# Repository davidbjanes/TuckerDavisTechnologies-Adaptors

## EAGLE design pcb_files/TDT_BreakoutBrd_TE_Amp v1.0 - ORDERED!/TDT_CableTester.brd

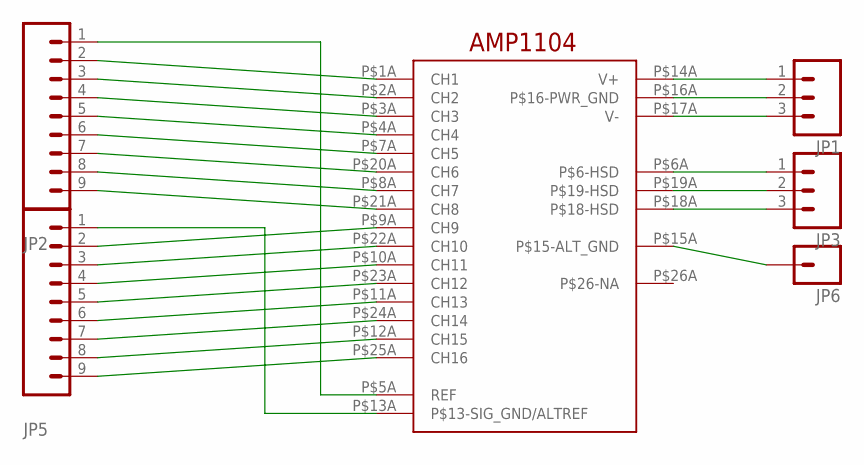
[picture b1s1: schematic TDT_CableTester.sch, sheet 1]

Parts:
JP1, JP3: M03PTH; 1X03
JP2, JP5: M09; 1X09
JP6: M01PTH; 1X01
U$3: AMP1104

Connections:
unnamed: JP2.2, U$3.P$1A (CH1)
unnamed: JP2.3, U$3.P$2A (CH2)
unnamed: JP2.4, U$3.P$3A (CH3)
unnamed: JP2.5, U$3.P$4A (CH4)
unnamed: JP2.6, U$3.P$7A (CH5)
unnamed: JP2.7, U$3.P$20A (CH6)
unnamed: JP2.8, U$3.P$8A (CH7)
unnamed: JP2.9, U$3.P$21A (CH8)
unnamed: JP5.2, U$3.P$9A (CH9)
unnamed: JP5.3, U$3.P$22A (CH10)
unnamed: JP5.4, U$3.P$10A (CH11)
unnamed: JP5.5, U$3.P$23A (CH12)
unnamed: JP5.6, U$3.P$11A (CH13)
unnamed: JP5.7, U$3.P$24A (CH14)
unnamed: JP5.8, U$3.P$12A (CH15)
unnamed: JP5.9, U$3.P$25A (CH16)
unnamed: JP1.1, U$3.P$14A (V+)
unnamed: JP1.2, U$3.P$16A (P$16-PWR_GND)
unnamed: JP1.3, U$3.P$17A (V-)
unnamed: JP6.1, U$3.P$15A (P$15-ALT_GND)
unnamed: JP2.1, U$3.P$5A (REF)
unnamed: JP5.1, U$3.P$13A (P$13-SIG_GND/ALTREF)
unnamed: JP3.1, U$3.P$6A (P$6-HSD)
unnamed: JP3.2, U$3.P$19A (P$19-HSD)
unnamed: JP3.3, U$3.P$18A (P$18-HSD)

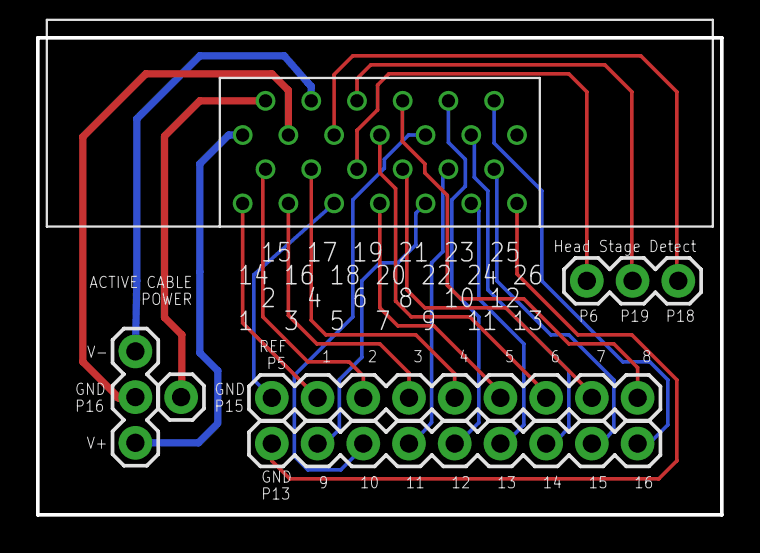
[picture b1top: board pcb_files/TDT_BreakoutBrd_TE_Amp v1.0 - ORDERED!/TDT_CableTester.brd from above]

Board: 2 copper layers, 38.0 x 26.5 mm, 6 parts (0 on the bottom side), 25 nets.

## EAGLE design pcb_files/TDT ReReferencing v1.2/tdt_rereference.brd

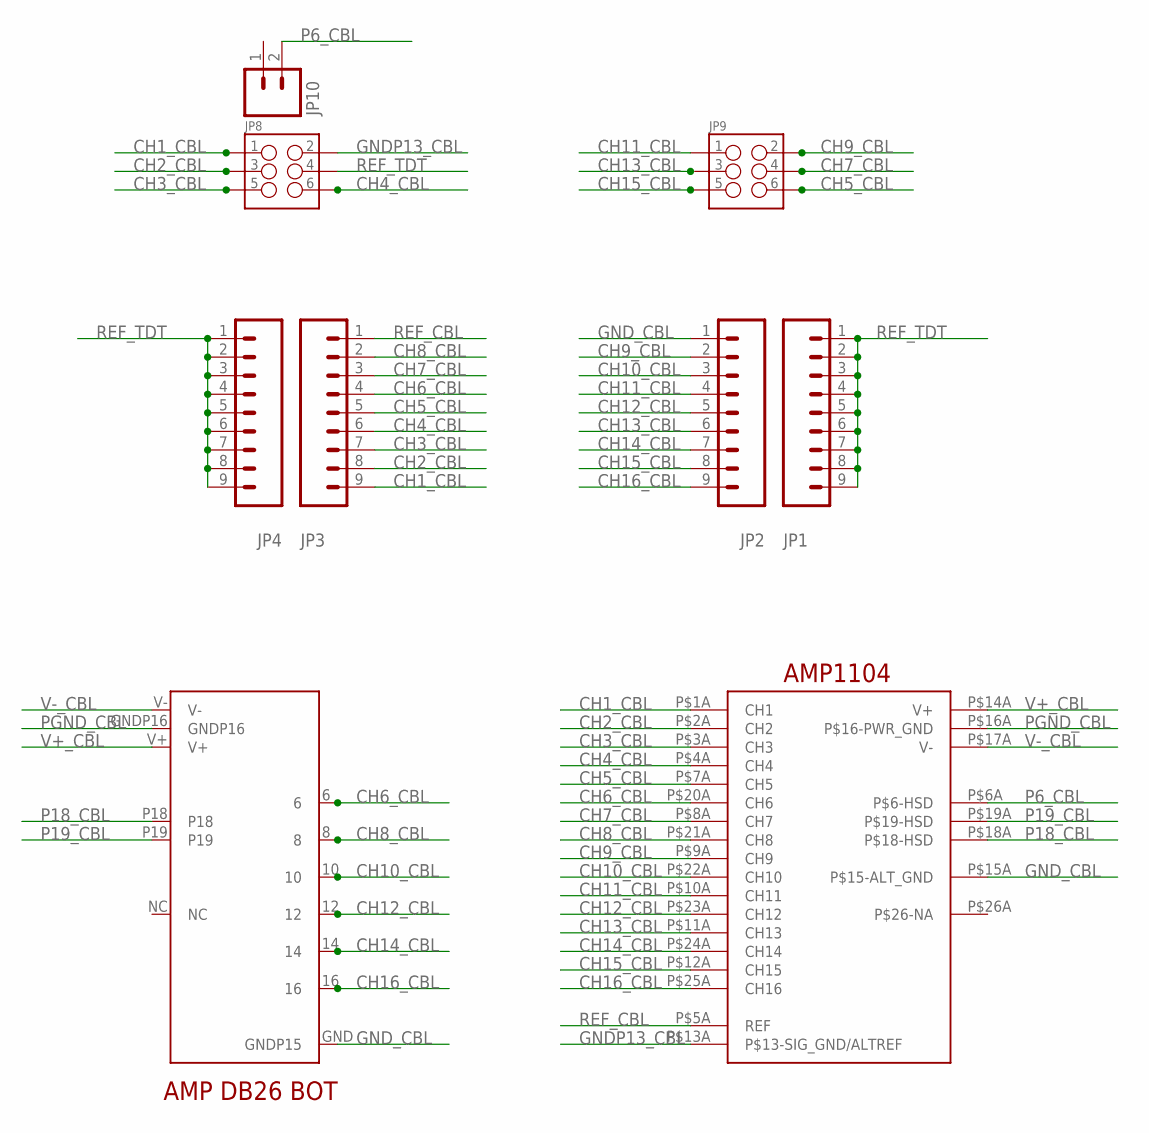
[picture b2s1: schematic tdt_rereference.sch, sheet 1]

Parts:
JP1, JP2, JP3, JP4: M09; 1X09
JP8, JP9: M03X22X3_SILK_MALE_PTH; 2X3
JP10: M02PTH; 1X02
U$1: DB26-MALE-BOT
U$3: AMP1104

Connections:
CH1_CBL: JP3.9, JP8.1, U$3.P$1A (CH1)
CH2_CBL: JP3.8, JP8.3, U$3.P$2A (CH2)
CH3_CBL: JP3.7, JP8.5, U$3.P$3A (CH3)
CH4_CBL: JP3.6, JP8.6, U$3.P$4A (CH4)
CH5_CBL: JP3.5, JP9.6, U$3.P$7A (CH5)
CH6_CBL: JP3.4, U$1.6, U$3.P$20A (CH6)
CH7_CBL: JP3.3, JP9.4, U$3.P$8A (CH7)
CH8_CBL: JP3.2, U$1.8, U$3.P$21A (CH8)
CH9_CBL: JP2.2, JP9.2, U$3.P$9A (CH9)
CH10_CBL: JP2.3, U$1.10, U$3.P$22A (CH10)
CH11_CBL: JP2.4, JP9.1, U$3.P$10A (CH11)
CH12_CBL: JP2.5, U$1.12, U$3.P$23A (CH12)
CH13_CBL: JP2.6, JP9.3, U$3.P$11A (CH13)
CH14_CBL: JP2.7, U$1.14, U$3.P$24A (CH14)
CH15_CBL: JP2.8, JP9.5, U$3.P$12A (CH15)
CH16_CBL: JP2.9, U$1.16, U$3.P$25A (CH16)
GNDP13_CBL: JP8.2, U$3.P$13A (P$13-SIG_GND/ALTREF)
GND_CBL: JP2.1, U$1.GND (GNDP15), U$3.P$15A (P$15-ALT_GND)
P6_CBL: JP10.2, U$3.P$6A (P$6-HSD)
P18_CBL: U$1.P18, U$3.P$18A (P$18-HSD)
P19_CBL: U$1.P19, U$3.P$19A (P$19-HSD)
PGND_CBL: U$1.GNDP16, U$3.P$16A (P$16-PWR_GND)
REF_CBL: JP3.1, U$3.P$5A (REF)
REF_TDT: JP1.1, JP1.2, JP1.3, JP1.4, JP1.5, JP1.6, JP1.7, JP1.8, JP1.9, JP4.1, JP4.2, JP4.3, JP4.4, JP4.5, JP4.6, JP4.7, JP4.8, JP4.9, JP8.4
V+_CBL: U$1.V+, U$3.P$14A (V+)
V-_CBL: U$1.V-, U$3.P$17A (V-)

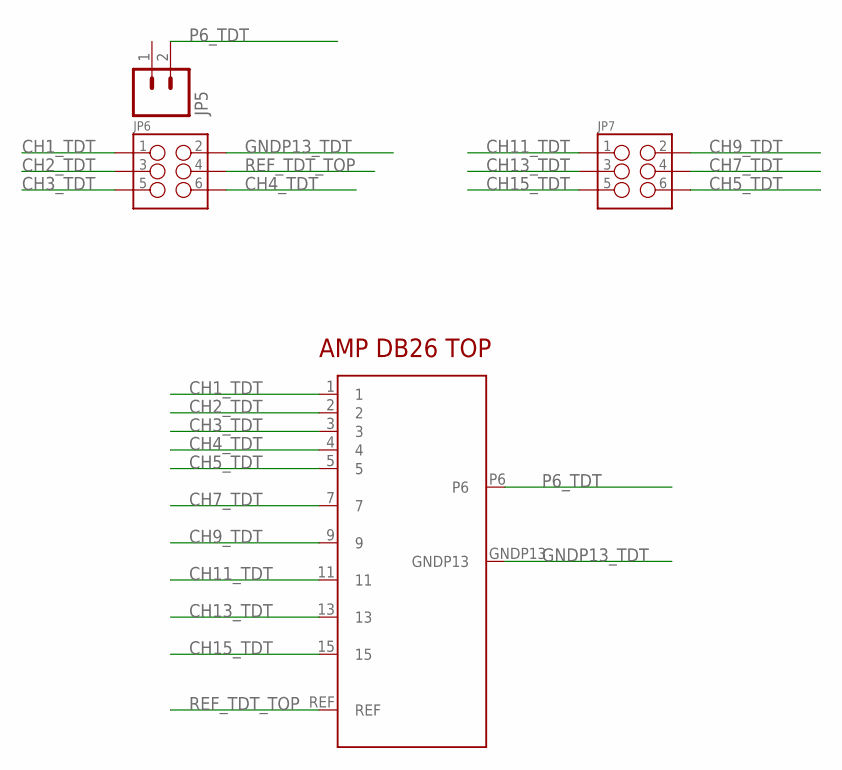
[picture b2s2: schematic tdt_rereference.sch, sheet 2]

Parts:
JP5: M02PTH; 1X02
JP6, JP7: M03X22X3_SILK_MALE_PTH; 2X3
U$2: DB26-MALE-TOP

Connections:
CH1_TDT: JP6.1, U$2.1
CH2_TDT: JP6.3, U$2.2
CH3_TDT: JP6.5, U$2.3
CH4_TDT: JP6.6, U$2.4
CH5_TDT: JP7.6, U$2.5
CH7_TDT: JP7.4, U$2.7
CH9_TDT: JP7.2, U$2.9
CH11_TDT: JP7.1, U$2.11
CH13_TDT: JP7.3, U$2.13
CH15_TDT: JP7.5, U$2.15
GNDP13_TDT: JP6.2, U$2.GNDP13
P6_TDT: JP5.2, U$2.P6
REF_TDT_TOP: JP6.4, U$2.REF

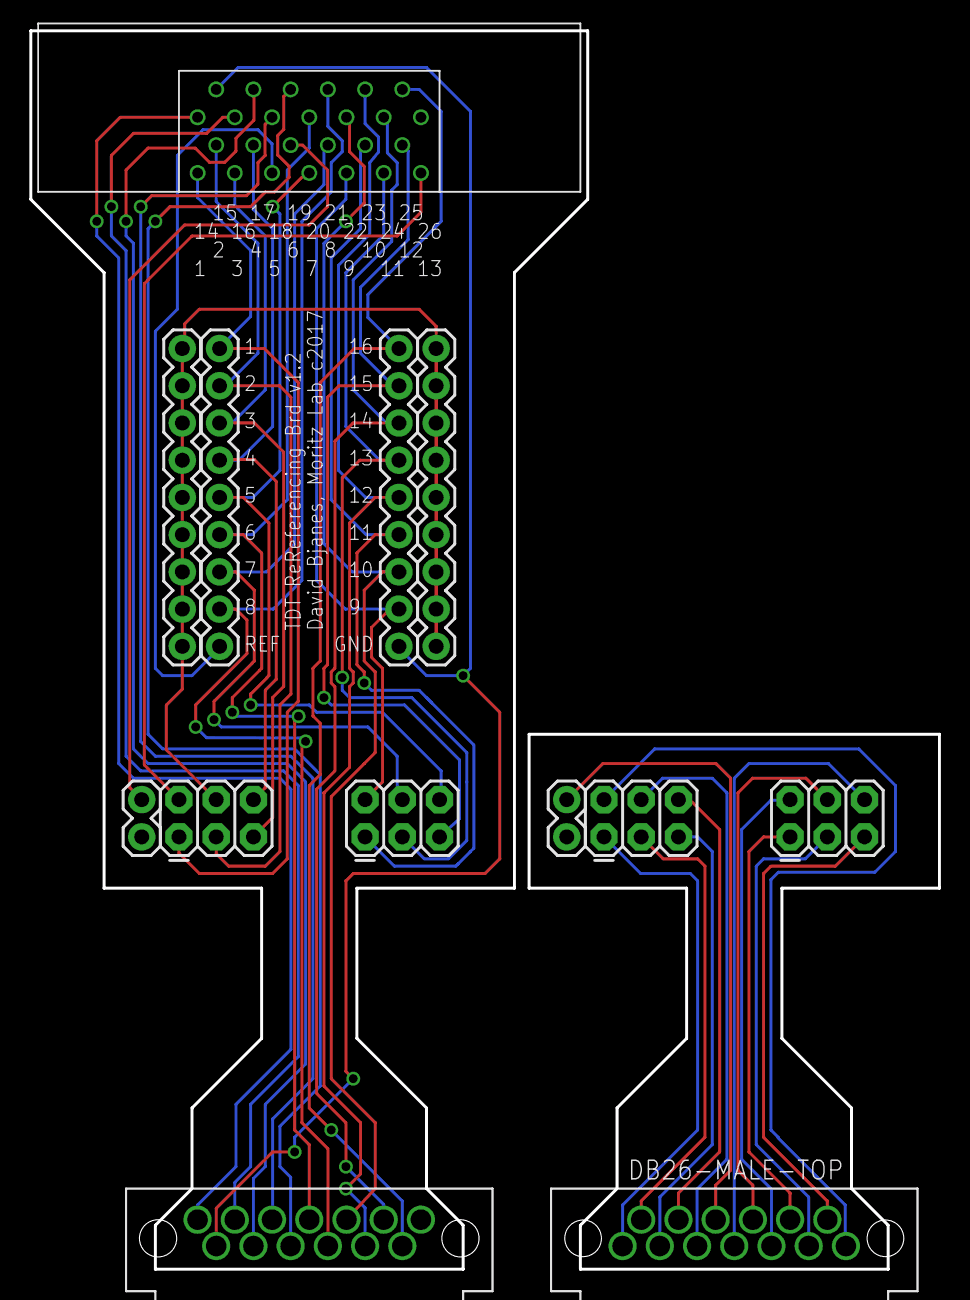
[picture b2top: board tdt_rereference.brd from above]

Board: 2 copper layers, 62.0 x 84.5 mm, 13 parts (0 on the bottom side), 39 nets.

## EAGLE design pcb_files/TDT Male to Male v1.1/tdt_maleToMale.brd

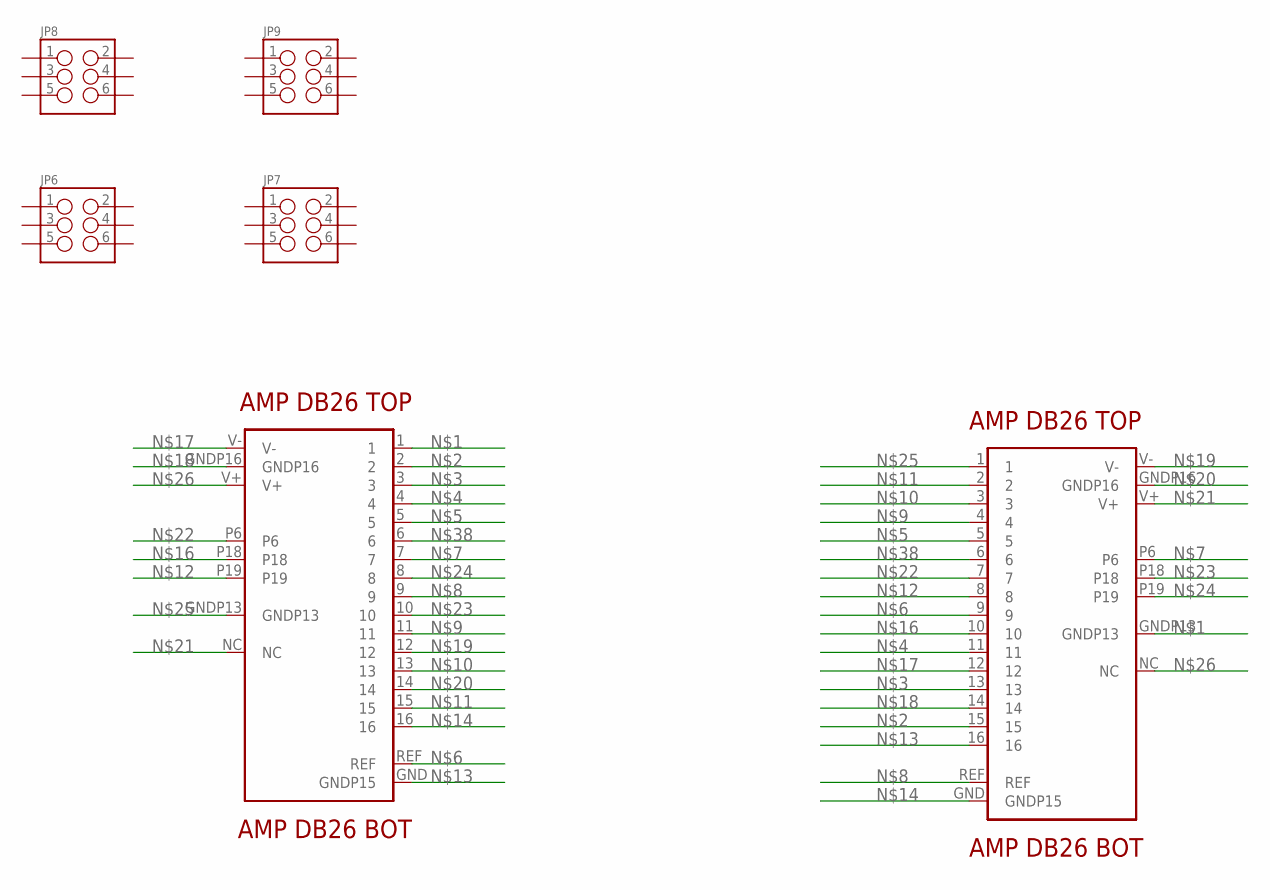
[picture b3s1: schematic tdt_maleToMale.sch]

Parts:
JP6, JP7, JP8, JP9: M03X22X3_SILK_MALE_PTH; 2X3
U$1, U$4: DB26-MALE-BOT
U$2, U$3: DB26-MALE-TOP

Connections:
unnamed: U$2.1, U$3.GNDP13
unnamed: U$2.2, U$3.15
unnamed: U$2.3, U$3.13
unnamed: U$2.4, U$3.11
unnamed: U$2.5, U$3.5
unnamed: U$2.REF, U$3.9
unnamed: U$2.7, U$3.P6
unnamed: U$2.9, U$3.REF
unnamed: U$2.11, U$3.4
unnamed: U$2.13, U$3.3
unnamed: U$2.15, U$3.2
unnamed: U$1.P19, U$4.8
unnamed: U$1.GND (GNDP15), U$4.16
unnamed: U$1.16, U$4.GND (GNDP15)
unnamed: U$1.P18, U$4.10
unnamed: U$1.V-, U$4.12
unnamed: U$1.GNDP16, U$4.14
unnamed: U$1.12, U$4.V-
unnamed: U$1.14, U$4.GNDP16
unnamed: U$1.NC, U$4.V+
unnamed: U$2.P6, U$3.7
unnamed: U$1.10, U$4.P18
unnamed: U$1.8, U$4.P19
unnamed: U$2.GNDP13, U$3.1
unnamed: U$1.V+, U$4.NC
unnamed: U$1.6, U$4.6

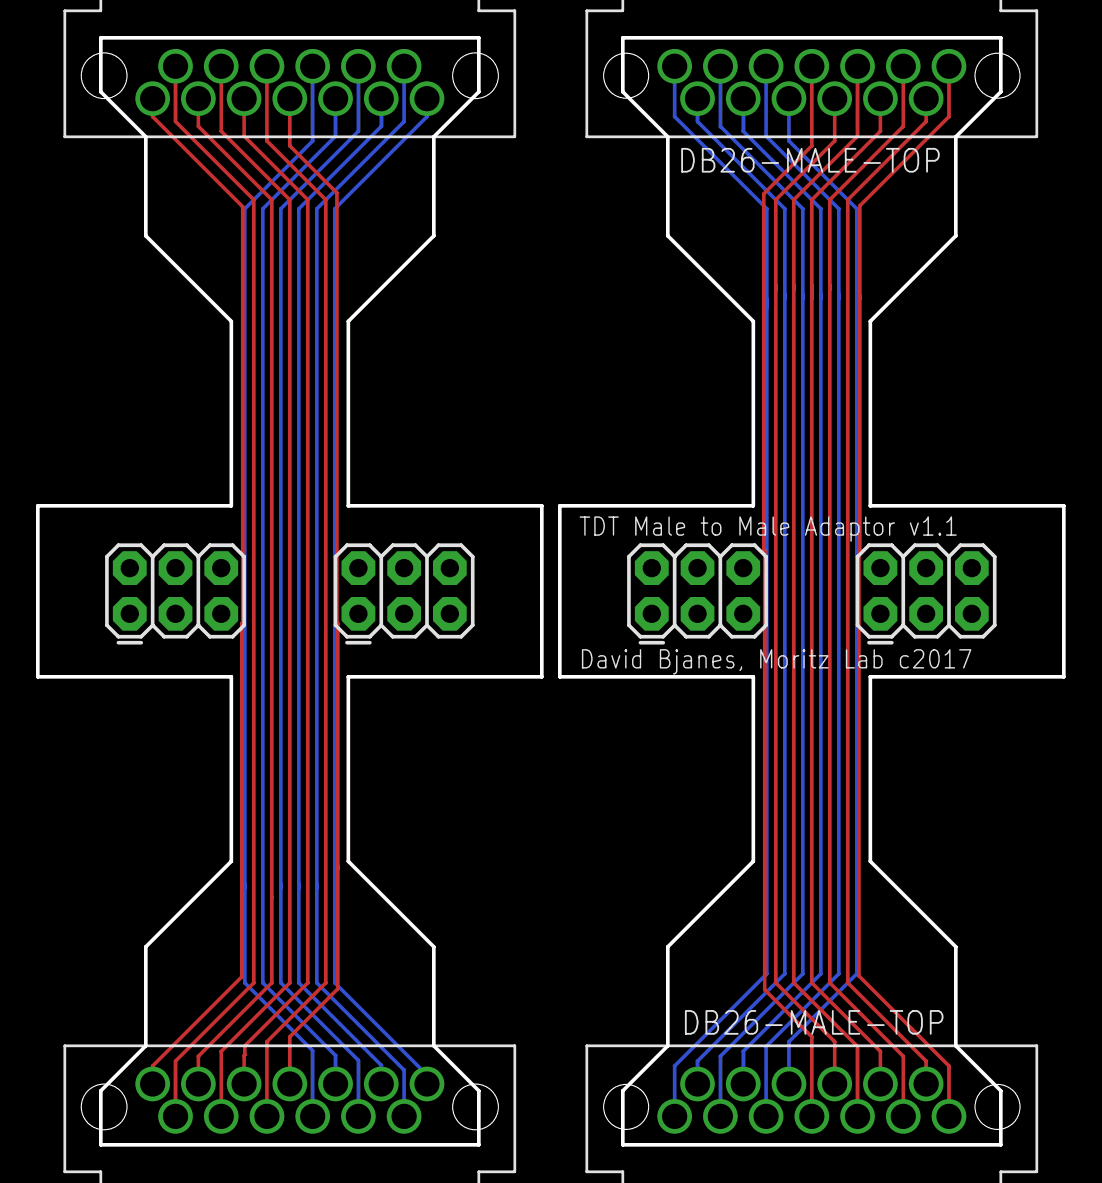
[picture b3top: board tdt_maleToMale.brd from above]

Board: 2 copper layers, 57.0 x 61.5 mm, 8 parts (0 on the bottom side), 26 nets.

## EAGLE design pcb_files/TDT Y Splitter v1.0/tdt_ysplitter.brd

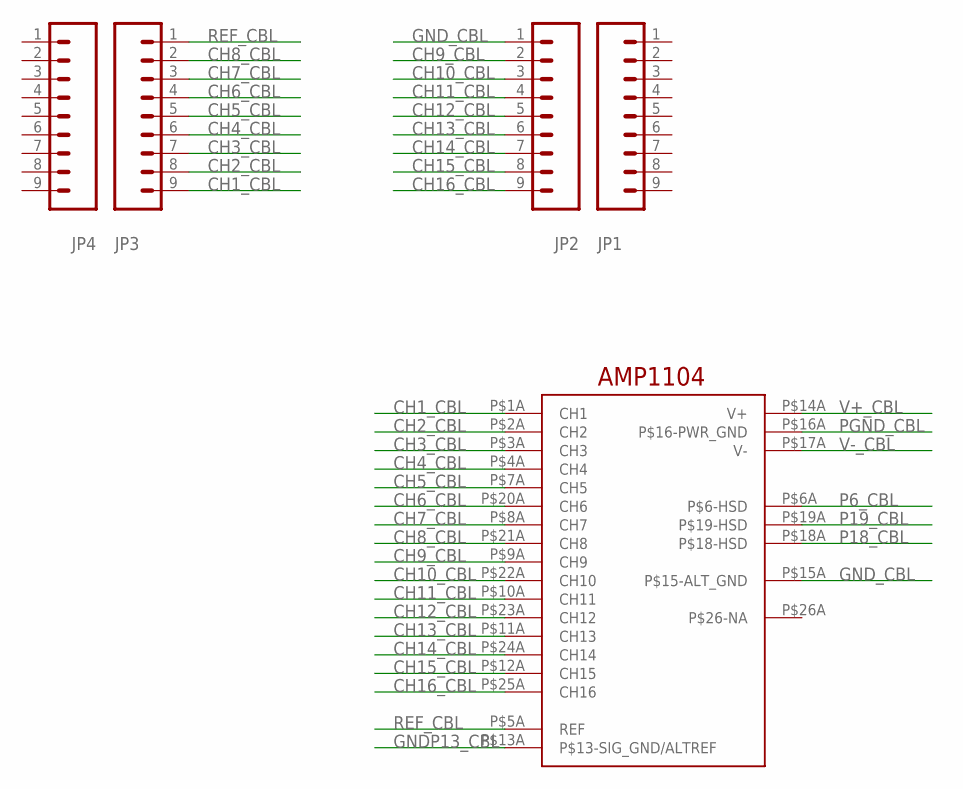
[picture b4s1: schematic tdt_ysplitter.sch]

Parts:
JP1, JP2, JP3, JP4: M09; 1X09
U$3: AMP1104

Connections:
CH1_CBL: JP3.9, U$3.P$1A (CH1)
CH2_CBL: JP3.8, U$3.P$2A (CH2)
CH3_CBL: JP3.7, U$3.P$3A (CH3)
CH4_CBL: JP3.6, U$3.P$4A (CH4)
CH5_CBL: JP3.5, U$3.P$7A (CH5)
CH6_CBL: JP3.4, U$3.P$20A (CH6)
CH7_CBL: JP3.3, U$3.P$8A (CH7)
CH8_CBL: JP3.2, U$3.P$21A (CH8)
CH9_CBL: JP2.2, U$3.P$9A (CH9)
CH10_CBL: JP2.3, U$3.P$22A (CH10)
CH11_CBL: JP2.4, U$3.P$10A (CH11)
CH12_CBL: JP2.5, U$3.P$23A (CH12)
CH13_CBL: JP2.6, U$3.P$11A (CH13)
CH14_CBL: JP2.7, U$3.P$24A (CH14)
CH15_CBL: JP2.8, U$3.P$12A (CH15)
CH16_CBL: JP2.9, U$3.P$25A (CH16)
GNDP13_CBL: U$3.P$13A (P$13-SIG_GND/ALTREF)
GND_CBL: JP2.1, U$3.P$15A (P$15-ALT_GND)
P6_CBL: U$3.P$6A (P$6-HSD)
P18_CBL: U$3.P$18A (P$18-HSD)
P19_CBL: U$3.P$19A (P$19-HSD)
PGND_CBL: U$3.P$16A (P$16-PWR_GND)
REF_CBL: JP3.1, U$3.P$5A (REF)
V+_CBL: U$3.P$14A (V+)
V-_CBL: U$3.P$17A (V-)

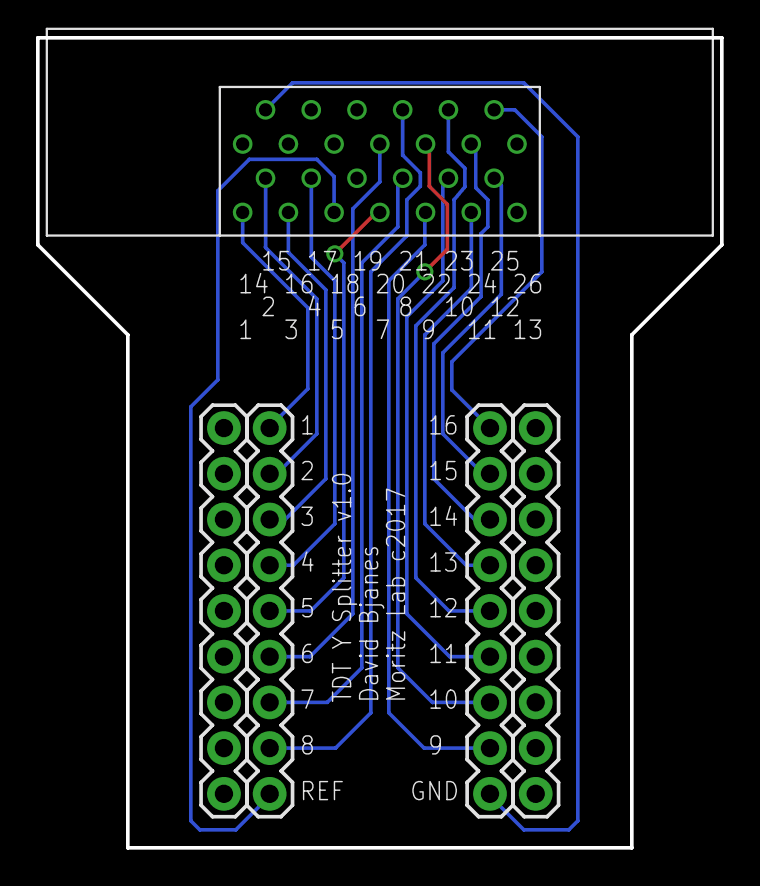
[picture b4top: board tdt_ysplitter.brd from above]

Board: 2 copper layers, 38.0 x 45.0 mm, 5 parts (0 on the bottom side), 18 nets.

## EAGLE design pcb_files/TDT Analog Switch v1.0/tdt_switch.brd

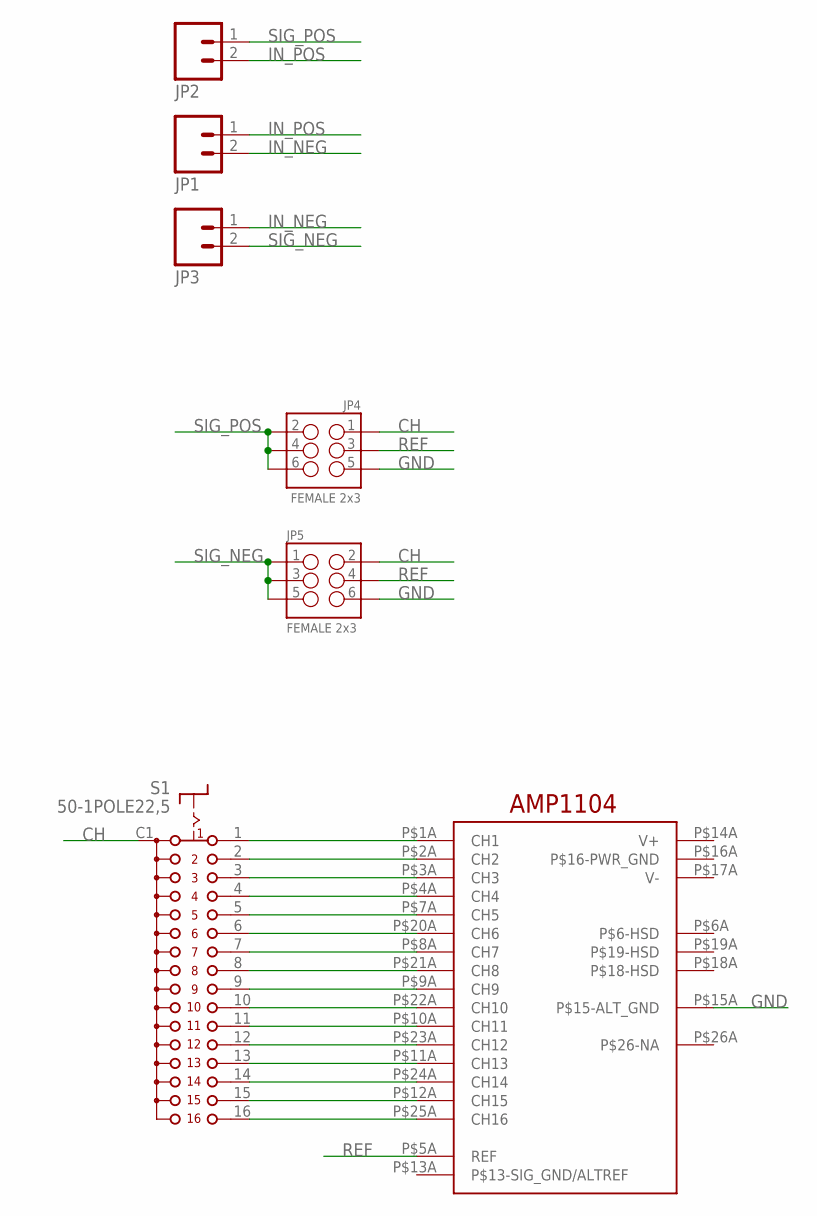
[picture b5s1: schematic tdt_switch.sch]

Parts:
JP1, JP2, JP3: M02PTH; 1X02
JP4, JP5: FEMALE 2x3; 2X3
S1: 50-1POLE22,5
U$3: AMP1104

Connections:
CH: JP4.1, JP5.2, S1.C1 (C)
GND: JP4.5, JP5.6, U$3.P$15A (P$15-ALT_GND)
IN_NEG: JP1.2, JP3.1
IN_POS: JP1.1, JP2.2
unnamed: S1.1, U$3.P$1A (CH1)
unnamed: S1.2, U$3.P$2A (CH2)
unnamed: S1.3, U$3.P$3A (CH3)
unnamed: S1.4, U$3.P$4A (CH4)
unnamed: S1.5, U$3.P$7A (CH5)
unnamed: S1.6, U$3.P$20A (CH6)
unnamed: S1.7, U$3.P$8A (CH7)
unnamed: S1.8, U$3.P$21A (CH8)
unnamed: S1.9, U$3.P$9A (CH9)
unnamed: S1.10, U$3.P$22A (CH10)
unnamed: S1.11, U$3.P$10A (CH11)
unnamed: S1.12, U$3.P$23A (CH12)
unnamed: S1.13, U$3.P$11A (CH13)
unnamed: S1.14, U$3.P$24A (CH14)
unnamed: S1.15, U$3.P$12A (CH15)
unnamed: S1.16, U$3.P$25A (CH16)
REF: JP4.3, JP5.4, U$3.P$5A (REF)
SIG_NEG: JP3.2, JP5.1, JP5.3, JP5.5
SIG_POS: JP2.1, JP4.2, JP4.4, JP4.6

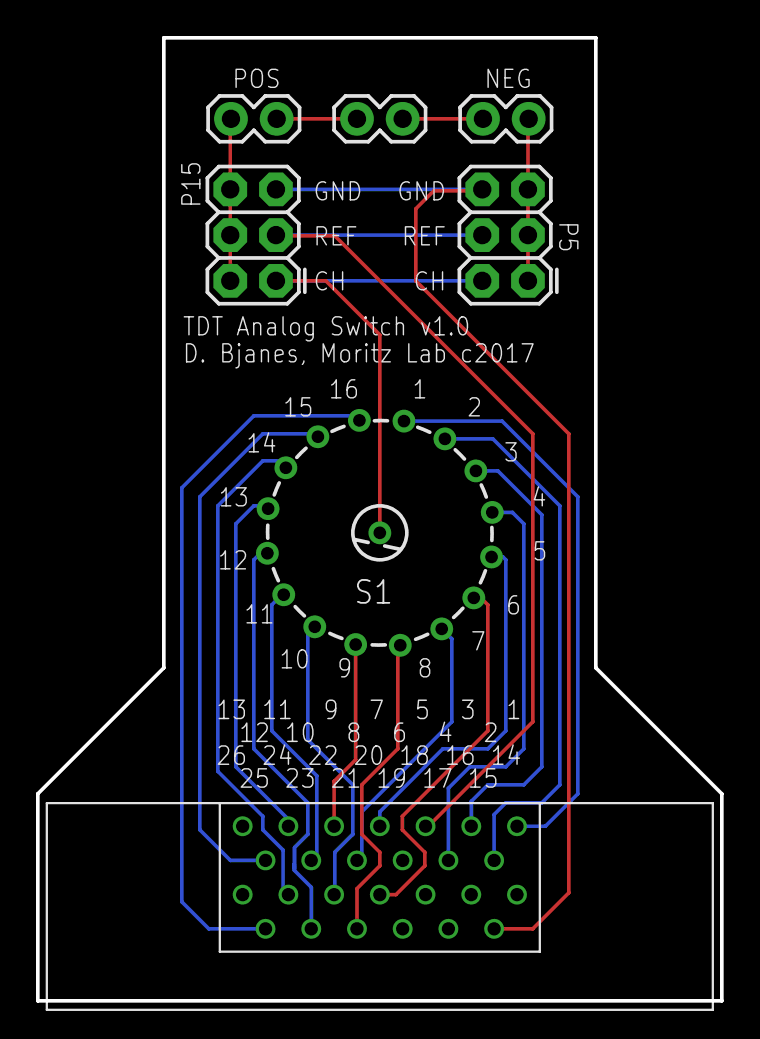
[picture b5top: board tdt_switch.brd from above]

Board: 2 copper layers, 38.0 x 53.5 mm, 7 parts (0 on the bottom side), 23 nets.

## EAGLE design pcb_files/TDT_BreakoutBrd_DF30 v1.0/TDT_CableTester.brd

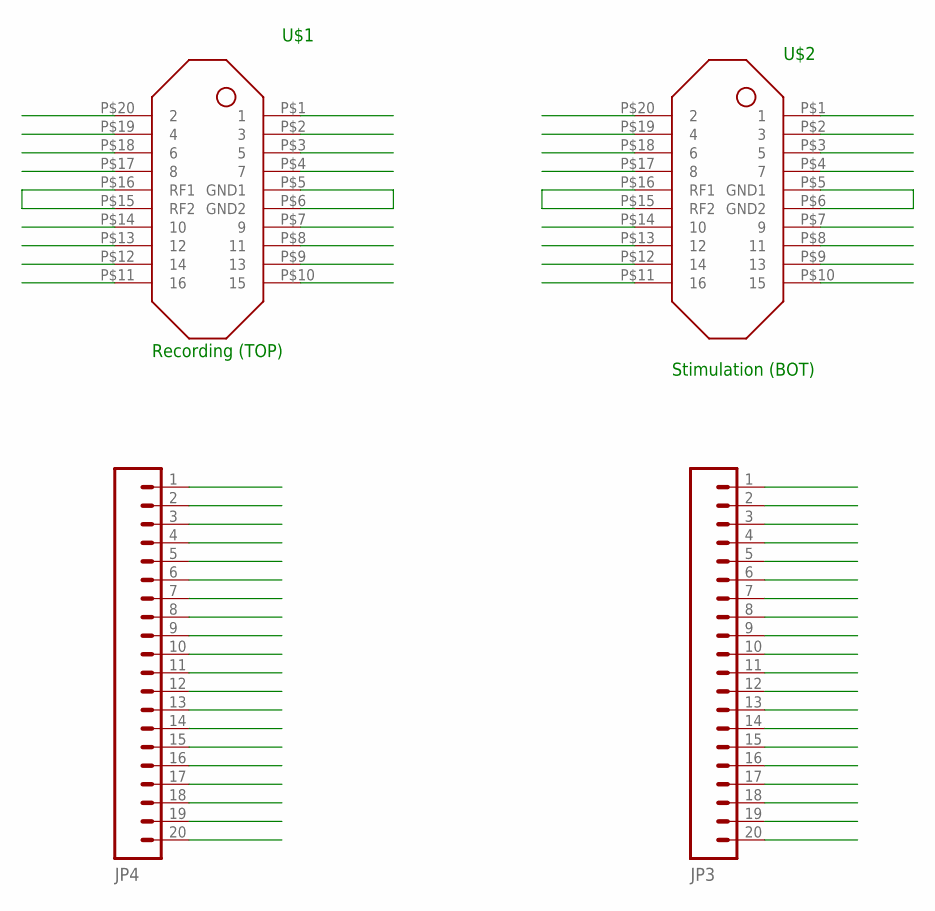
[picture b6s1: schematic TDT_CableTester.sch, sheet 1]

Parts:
JP3, JP4: M20; 1X20
U$1, U$2: DF30_HEADER; DF30FC-20DP-0.4V

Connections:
B1: JP3.1, U$2.P$1 (1)
B2: JP3.2, U$2.P$20 (2)
B3: JP3.3, U$2.P$2 (3)
B4: JP3.4, U$2.P$19 (4)
B5: JP3.5, U$2.P$3 (5)
B6: JP3.6, U$2.P$18 (6)
B7: JP3.7, U$2.P$4 (7)
B8: JP3.8, U$2.P$17 (8)
B9: JP3.9, U$2.P$7 (9)
B10: JP3.10, U$2.P$14 (10)
B11: JP3.11, U$2.P$8 (11)
B12: JP3.12, U$2.P$13 (12)
B13: JP3.13, U$2.P$9 (13)
B14: JP3.14, U$2.P$12 (14)
B15: JP3.15, U$2.P$10 (15)
B16: JP3.16, U$2.P$11 (16)
BG1: JP3.19, U$2.P$5 (GND1), U$2.P$6 (GND2)
BG2: JP3.20
BRF1: JP3.17, U$2.P$15 (RF2), U$2.P$16 (RF1)
BRF2: JP3.18
T1: JP4.1, U$1.P$1 (1)
T2: JP4.2, U$1.P$20 (2)
T3: JP4.3, U$1.P$2 (3)
T4: JP4.4, U$1.P$19 (4)
T5: JP4.5, U$1.P$3 (5)
T6: JP4.6, U$1.P$18 (6)
T7: JP4.7, U$1.P$4 (7)
T8: JP4.8, U$1.P$17 (8)
T9: JP4.9, U$1.P$7 (9)
T10: JP4.10, U$1.P$14 (10)
T11: JP4.11, U$1.P$8 (11)
T12: JP4.12, U$1.P$13 (12)
T13: JP4.13, U$1.P$9 (13)
T14: JP4.14, U$1.P$12 (14)
T15: JP4.15, U$1.P$10 (15)
T16: JP4.16, U$1.P$11 (16)
TG1: JP4.19, U$1.P$5 (GND1), U$1.P$6 (GND2)
TG2: JP4.20
TRF1: JP4.17, U$1.P$15 (RF2), U$1.P$16 (RF1)
TRF2: JP4.18

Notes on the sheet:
U$2
U$1
Recording (TOP)
Stimulation (BOT)

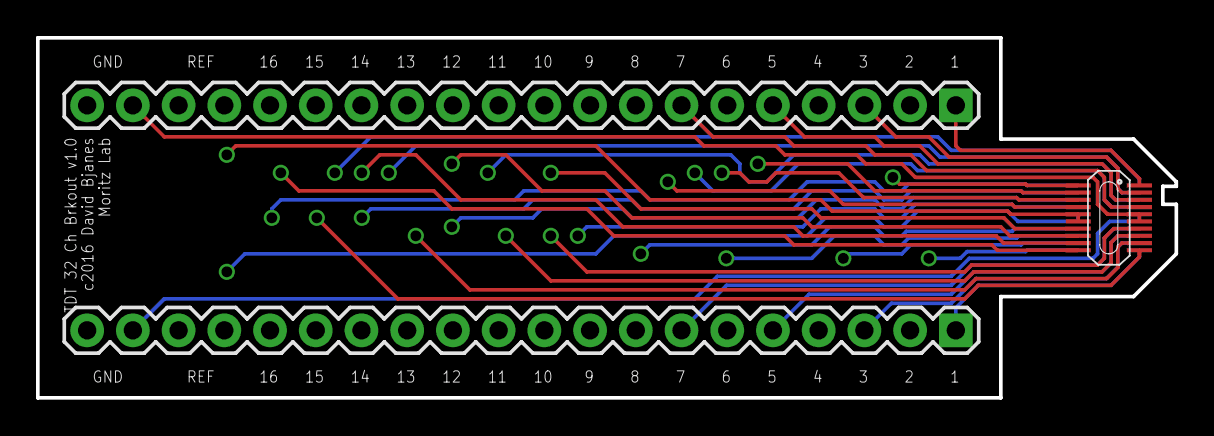
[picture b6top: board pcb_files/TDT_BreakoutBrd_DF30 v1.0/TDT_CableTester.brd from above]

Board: 4 copper layers, 63.2 x 20.0 mm, 4 parts (1 on the bottom side), 36 nets.

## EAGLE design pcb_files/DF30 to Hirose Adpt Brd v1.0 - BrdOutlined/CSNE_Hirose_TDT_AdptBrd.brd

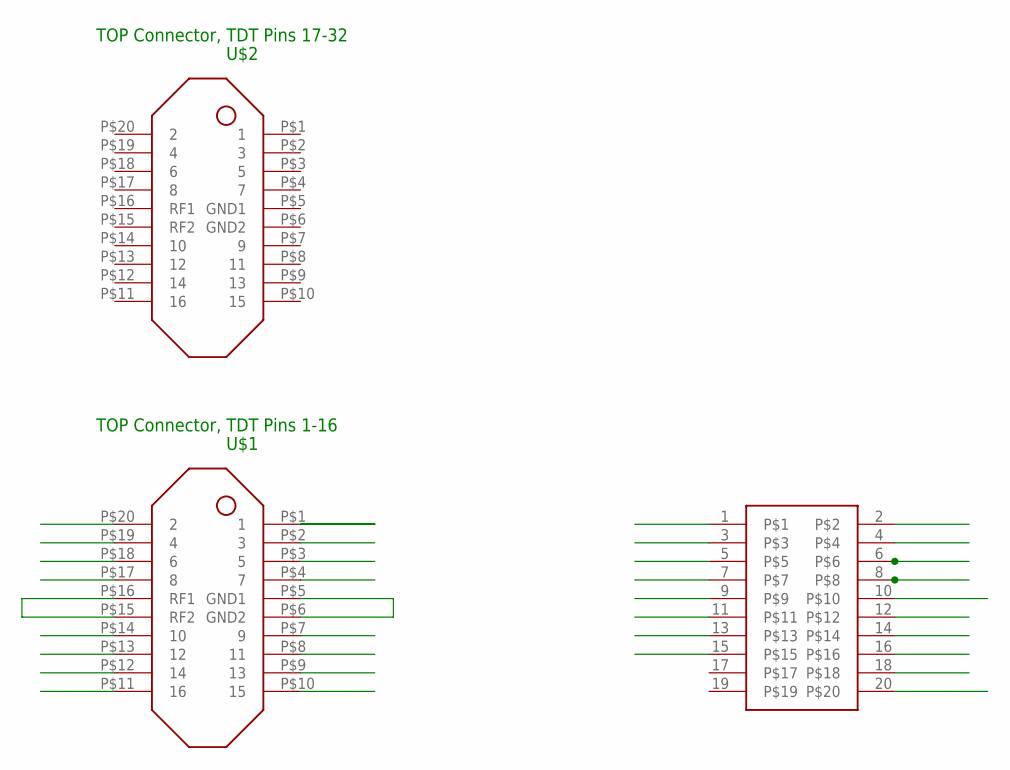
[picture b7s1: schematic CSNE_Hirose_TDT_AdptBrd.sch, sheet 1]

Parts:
U$1, U$2: DF30_HEADER; DF30FC-20DP-0.4V
U$3: CON-DF17-20F

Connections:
unnamed: U$1.P$1 (1), U$3.1
unnamed: U$1.P$2 (3), U$3.3
unnamed: U$1.P$3 (5), U$3.5
unnamed: U$1.P$4 (7), U$3.7
unnamed: U$1.P$5 (GND1), U$1.P$6 (GND2), U$3.20
unnamed: U$1.P$7 (9), U$3.9
unnamed: U$1.P$8 (11), U$3.11
unnamed: U$1.P$9 (13), U$3.13
unnamed: U$1.P$10 (15), U$3.15
unnamed: U$1.P$11 (16), U$3.18
unnamed: U$1.P$12 (14), U$3.16
unnamed: U$1.P$13 (12), U$3.14
unnamed: U$1.P$14 (10), U$3.12
unnamed: U$1.P$15 (RF2), U$1.P$16 (RF1), U$3.10
unnamed: U$1.P$17 (8), U$3.8
unnamed: U$1.P$18 (6), U$3.6
unnamed: U$1.P$19 (4), U$3.4
unnamed: U$1.P$20 (2), U$3.2

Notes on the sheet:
U$2
U$1
TOP Connector, TDT Pins 1-16
TOP Connector, TDT Pins 17-32

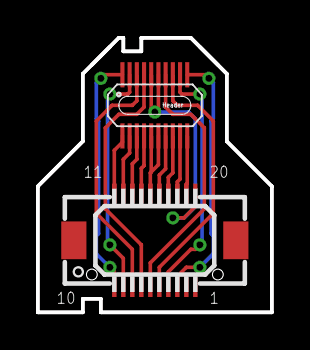
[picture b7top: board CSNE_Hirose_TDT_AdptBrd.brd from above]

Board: 4 copper layers, 13.0 x 15.2 mm, 3 parts (1 on the bottom side), 18 nets.

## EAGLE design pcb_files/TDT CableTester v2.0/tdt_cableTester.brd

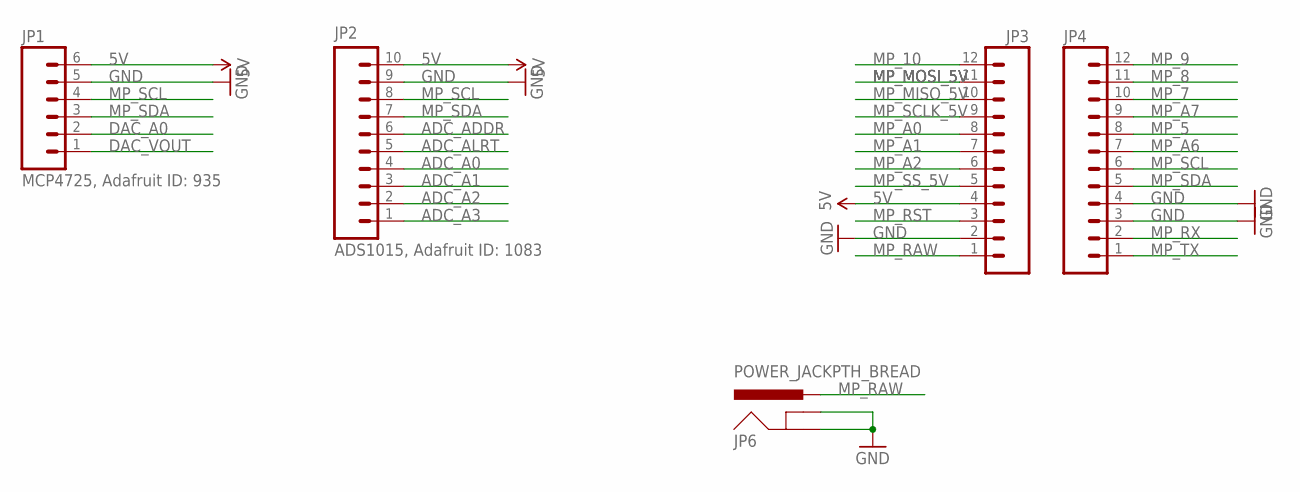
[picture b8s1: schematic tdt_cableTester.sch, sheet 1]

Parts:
JP1: MCP4725, Adafruit ID: 935; 1X06
JP2: ADS1015, Adafruit ID: 1083; 1X10
JP3, JP4: M12PTH; 1X12
JP6: POWER_JACKPTH_BREAD; POWER_JACK_PTH_BREAD

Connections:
5V: JP1.6, JP2.10, JP3.4; also elsewhere on the board
ADC_A0: JP2.4
ADC_A1: JP2.3; also elsewhere on the board
ADC_A2: JP2.2; also elsewhere on the board
ADC_A3: JP2.1; also elsewhere on the board
ADC_ADDR: JP2.6
ADC_ALRT: JP2.5
DAC_A0: JP1.2
DAC_VOUT: JP1.1; also elsewhere on the board
GND: JP1.5, JP2.9, JP3.2, JP4.3, JP4.4, JP6.GND, JP6.GNDBREAK; also elsewhere on the board
MP_5: JP4.8; also elsewhere on the board
MP_7: JP4.10; also elsewhere on the board
MP_8: JP4.11; also elsewhere on the board
MP_9: JP4.12; also elsewhere on the board
MP_10: JP3.12; also elsewhere on the board
MP_A0: JP3.8; also elsewhere on the board
MP_A1: JP3.7; also elsewhere on the board
MP_A2: JP3.6; also elsewhere on the board
MP_A6: JP4.7; also elsewhere on the board
MP_A7: JP4.9; also elsewhere on the board
MP_MISO_5V: JP3.10; also elsewhere on the board
MP_MOSI_5V: JP3.11; also elsewhere on the board
MP_RAW: JP3.1, JP6.PWR
MP_RST: JP3.3
MP_RX: JP4.2
MP_SCL: JP1.4, JP2.8, JP4.6
MP_SCLK_5V: JP3.9; also elsewhere on the board
MP_SDA: JP1.3, JP2.7, JP4.5
MP_SS_5V: JP3.5; also elsewhere on the board
MP_TX: JP4.1

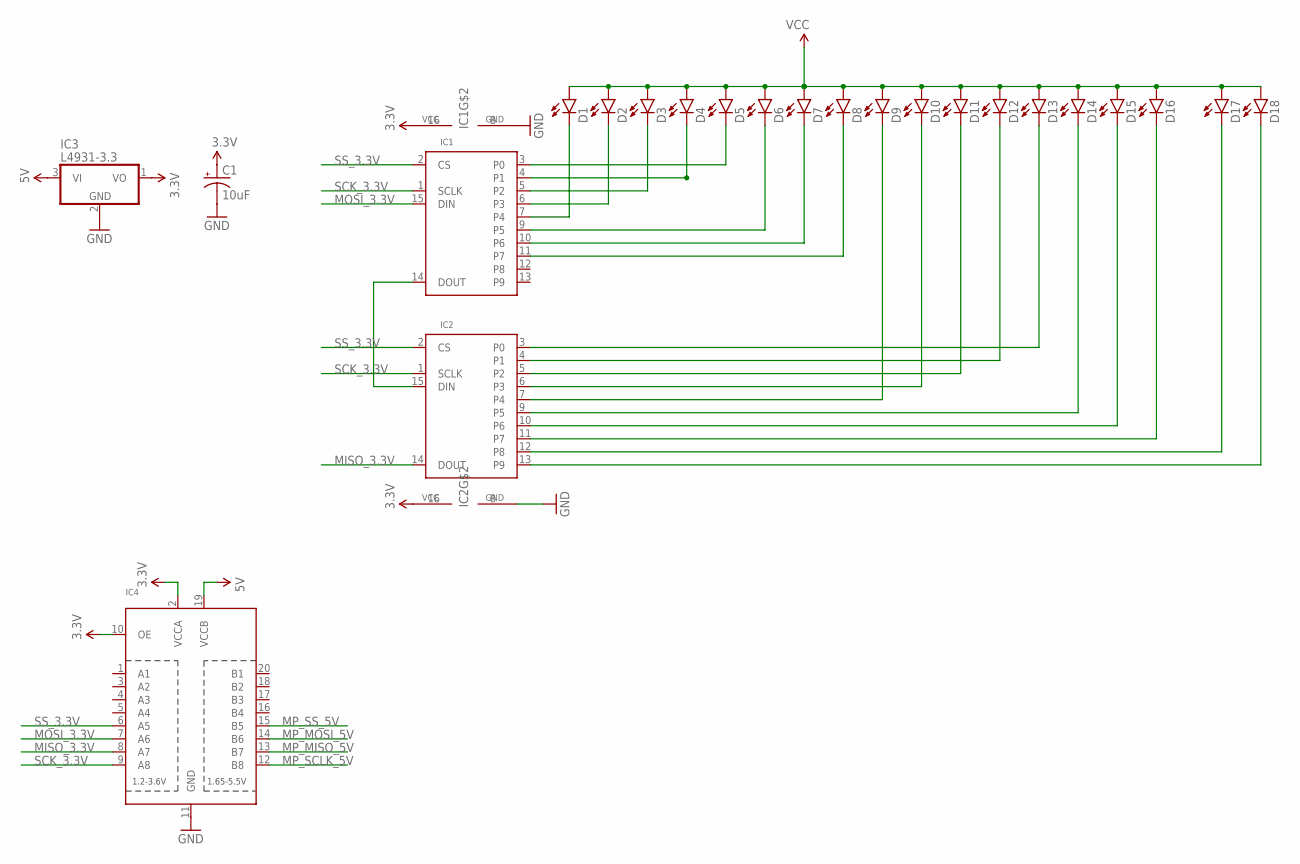
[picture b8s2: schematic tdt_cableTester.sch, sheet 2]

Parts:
C1: 10uF; CPOL-RADIAL-10UF-25V
D1, D2, D3, D4, D5, D6, D7, D8, D9, D10, D11, D12, D13, D14, D15, D16, D17, D18: LED1206; LED-1206
IC1, IC2: MAX6966AEE; QSOP16
IC3: L4931-3.3; TO92
IC4: TXB0108PWR; TSSOP20

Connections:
3.3V: C1.1 (+), IC1.16 (VCC), IC2.16 (VCC), IC3.1 (VO), IC4.2 (VCCA), IC4.10 (OE)
5V: D1.A, D2.A, D3.A, D4.A, D5.A, D6.A, D7.A, D8.A, D9.A, D10.A, D11.A, D12.A, D13.A, D14.A, D15.A, D16.A, D17.A, D18.A, IC3.3 (VI), IC4.19 (VCCB); also elsewhere on the board
DOUT_3.3V: IC1.14 (DOUT), IC2.15 (DIN)
GND: C1.2 (-), IC1.8 (GND), IC2.8 (GND), IC3.2 (GND), IC4.11 (GND); also elsewhere on the board
MISO_3.3V: IC2.14 (DOUT), IC4.8 (A7)
MOSI_3.3V: IC1.15 (DIN), IC4.7 (A6)
MP_MISO_5V: IC4.13 (B7); also elsewhere on the board
MP_MOSI_5V: IC4.14 (B6); also elsewhere on the board
MP_SCLK_5V: IC4.12 (B8); also elsewhere on the board
MP_SS_5V: IC4.15 (B5); also elsewhere on the board
unnamed: D9.C, IC2.7 (P4)
unnamed: D10.C, IC2.6 (P3)
unnamed: D11.C, IC2.5 (P2)
unnamed: D12.C, IC2.4 (P1)
unnamed: D13.C, IC2.3 (P0)
unnamed: D14.C, IC2.9 (P5)
unnamed: D5.C, IC1.3 (P0)
unnamed: D3.C, IC1.5 (P2)
unnamed: D2.C, IC1.6 (P3)
unnamed: D1.C, IC1.7 (P4)
unnamed: D6.C, IC1.9 (P5)
unnamed: D7.C, IC1.10 (P6)
unnamed: D8.C, IC1.11 (P7)
unnamed: D4.C, IC1.4 (P1)
unnamed: D16.C, IC2.11 (P7)
unnamed: D18.C, IC2.13 (P9)
unnamed: D15.C, IC2.10 (P6)
unnamed: D17.C, IC2.12 (P8)
SCK_3.3V: IC1.1 (SCLK), IC2.1 (SCLK), IC4.9 (A8)
SS_3.3V: IC1.2 (CS), IC2.2 (CS), IC4.6 (A5)

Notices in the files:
parts and their libraries:
SparkFun-Connectors: Licensing: Creative Commons ShareAlike 4.0 International - https://creativecommons.org/licenses/by-sa/4.0
